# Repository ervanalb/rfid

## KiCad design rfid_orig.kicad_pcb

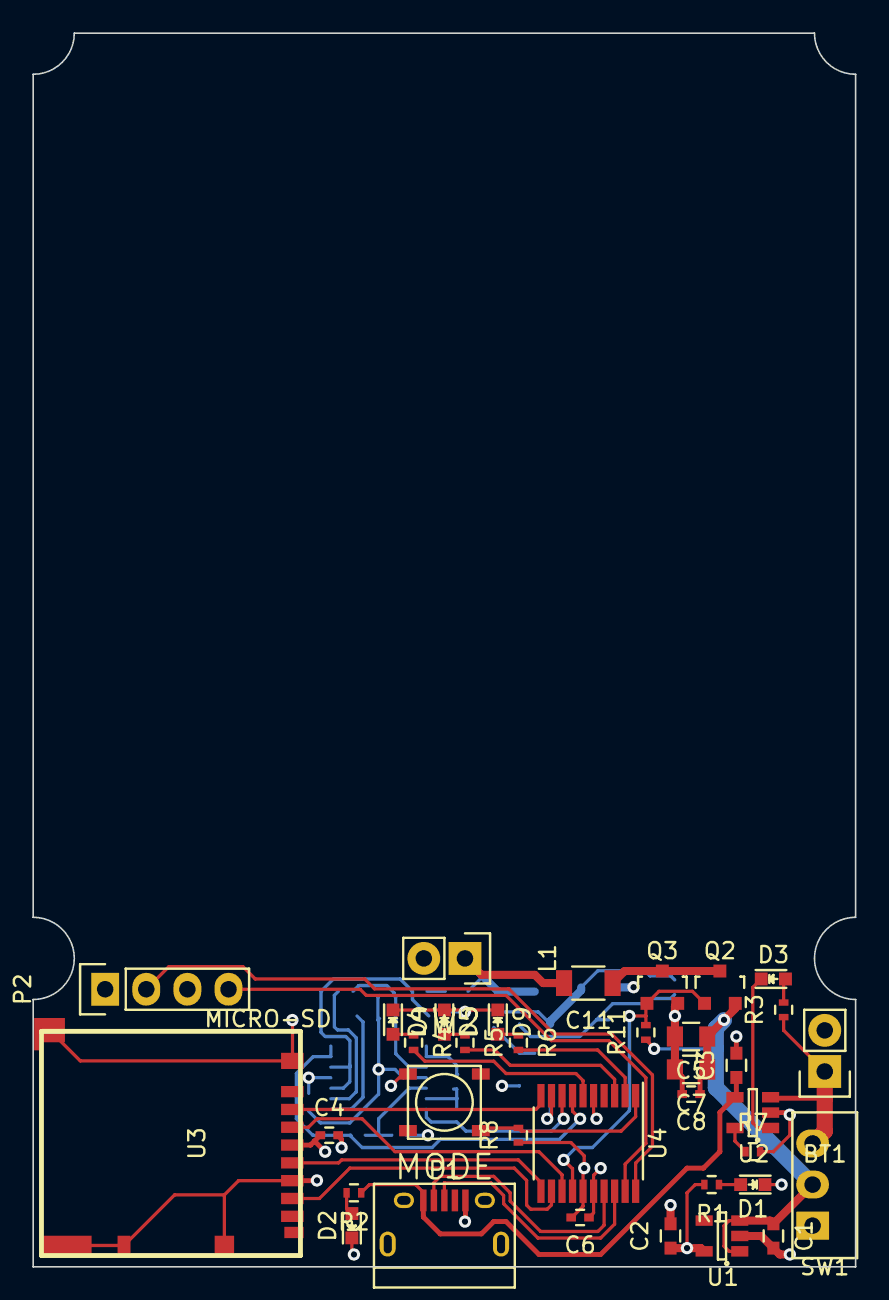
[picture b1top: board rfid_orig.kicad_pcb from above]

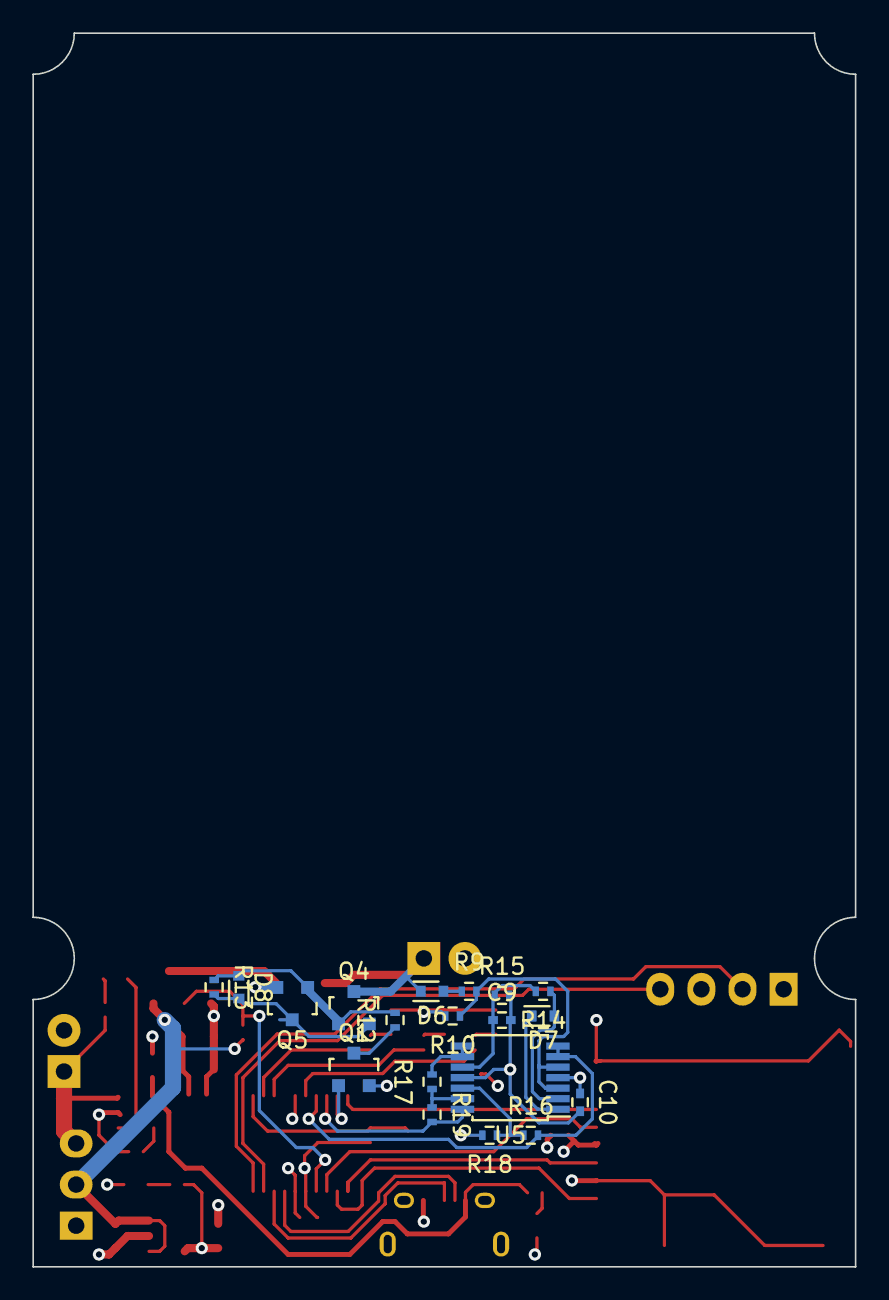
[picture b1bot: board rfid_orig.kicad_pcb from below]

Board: 4 copper layers, 50.8 x 76.2 mm, 55 parts (19 on the bottom side), 42 nets.

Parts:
BT1: BATTERY; Pin_Header_Straight_1x02
C1, C2, C3: 1u; C_0603
C4, C6, C8, C10: 100n; C_0402
C5: 47u; C_0805
C7: 2u2; C_0805
C9: 1n; C_0402
C11: 1n; C_1206
D1: PWR; LED_0603
D2: USB; LED_0603
D3: CHARGE; LED_0603
D4: READ; LED_0603
D5: WRITE; LED_0603
D6, D7: 1N4148; SOD-523
D8: 5V6; SOD-523
D9: SPOOF; LED_0603
L1: COIL; Pin_Header_Straight_1x02
P1: USB_OTG; USB_Micro-B
P2: SWD; Pin_Header_Straight_1x04
Q1, Q2: Q_PMOS_GSD; SOT-23
Q3, Q4, Q5: Q_NMOS_GSD; SOT-23
R1, R4, R5, R6: 330R; R_0402
R2: 680R; R_0402
R3: 560R; R_0402
R7: 2K2; R_0402
R8, R13: 100K; R_0402
R9, R15, R18, R19: 470K; R_0402
R10: 10K; R_0402
R11: 470R; R_0402
R12, R16, R17: 1K; R_0402
R14: 100R; R_0402
SW1: POWER; Pin_Header_Straight_1x03
SW2: MODE; TACT-SW-SMD
U1: MCP1824; SOT-23-5
U2: MCP7383X; SOT-23-5
U3: MICRO-SD; DM3BT
U4: STM32F030-20; TSSOP-20_4.4x6.5mm_Pitch0.65mm
U5: LM324; TSSOP-14_4.4x5mm_Pitch0.65mm

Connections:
+5V: C3.1, P1.1, R2.1, U2.4
+BATT: C1.1, C5.1, C7.1, C8.1, Q2.2, R11.1, SW1.2, U1.1, U1.3
/BOOT: R8.2, SW2.4, U4.1
/COIL_DETUNE: Q1.1, U4.9
/COIL_DRIVE: Q2.1, Q3.1, R11.2, U4.14
/COIL_READ: R19.2, U4.8, U5.14
/COIL_READ_AMP: R16.2, U4.7, U5.6, U5.7
/READ: R4.2, U4.6
/SPI_CS: U3.2, U4.10
/SPI_MISO: U3.7, U4.12
/SPI_MOSI: U3.3, U4.13
/SPI_SCK: U3.5, U4.11
/SPOOF: R6.2, U4.2
/SWCLK: P2.2, U4.20
/SWDAT: P2.4, U4.19
/USB_DM: P1.2, U4.17
/USB_DP: P1.3, U4.18
/WRITE: R5.2, U4.3
GND: BT1.2, C1.2, C2.2, C3.2, C4.2, C5.2, C6.2, C7.2, C8.2, C9.2, C10.2, D1.1, D2.1, D4.1, D5.1, D9.1, L1.2, P1.5, P1.6, P2.3, Q3.2, Q5.2, R7.2, R8.1, R10.2, R15.2, R18.2, U1.2, U2.2, U3.6, U3.9, U3.11, U3.12, U3.13, U3.14, U4.15, U5.11
unnamed: BT1.1, R3.1, SW1.3, U2.3
unnamed: C9.1, R14.2, R15.1, U5.10
unnamed: C11.1, Q2.3, Q3.3
unnamed: C11.2, D6.1, L1.1, Q4.3
unnamed: D1.2, R1.1
unnamed: D2.2, R2.2
unnamed: D3.1, U2.1
unnamed: D3.2, R3.2
unnamed: D4.2, R4.1
unnamed: D5.2, R5.1
unnamed: D6.2, R9.1
unnamed: D7.1, U5.1
unnamed: D7.2, R14.1, U5.2
unnamed: D8.1, Q4.2, Q5.3, R13.2
unnamed: D8.2, Q4.1, Q5.1, R12.2, R13.1
unnamed: D9.2, R6.1
unnamed: Q1.3, R12.1
unnamed: R7.1, U2.5
unnamed: R9.2, R10.1, U5.3, U5.5
unnamed: R16.1, R18.1, U5.12
unnamed: R17.1, R19.1, U5.13
unnamed: R17.2, U5.8, U5.9
VDD: C2.1, C4.1, C6.1, C10.1, P2.1, Q1.2, R1.2, SW2.1, U1.5, U3.4, U4.5, U4.16, U5.4

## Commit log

2016-11-13 usb enumerates
2016-11-14 USB control transfer to enable coil
2016-11-14 commit some broken code
2016-11-15 ADC DMA working
2016-11-15 configure TIM1 TRGO
2016-11-15 change latency to 75 and change DOS line endings to UNIX
2016-11-15 working on USB readout
2016-11-15 attempt to add bulk EP to descriptor
2016-11-18 reading PSK tags with python is working
2016-11-30 fix DMA read error, change python in non important ways
2016-12-11 python decoders for PSK, FSK
2017-02-21 USB tweaks to firmware
2017-02-21 add USB OUT enpoint (maybe)
2017-02-21 fix a few small USB issues and get python up to date
2017-02-21 sending data to card appears to work now
2017-02-23 add set_latency command, improve how latency works
2017-02-23 commit python before I accidentally delete it
2017-02-23 slowly improving python code
2017-02-24 move to numpy for signal processing, remove lpf
2017-02-24 writing and reading working well
2017-02-24 more compact pretty-print bytes
2017-02-24 remove unnecessary casts to list
2017-02-26 read/write HID cards working (FSK)
2017-03-02 work on a clock recovery algorithm, begin stubbing out main firmware functionality
2017-03-02 actually add firmware files
2017-03-02 start decoding PSK in firmware
2017-03-04 check for valid reads of PSK
2017-03-04 cycle sorting
2017-03-04 begin stubbing out write SM
2017-03-05 write card firmware working
2017-03-05 add better button UI
2017-03-05 add better LED ui
2017-03-05 introduce much more efficient cycle sorting algorithm
2017-03-12 add chan's fatfs, move some protocol_state into protocol_params
2017-07-02 start working on SD card stuff
